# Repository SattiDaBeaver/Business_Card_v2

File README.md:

# RISC-V Supercluster Business Card

A business-card-sized PCB featuring a miniature distributed compute cluster with one master MCU coordinating eight worker nodes over a shared UART bus, powered and programmed entirely through a PCB-edge USB-C connector.

Inspired by distributed systems, Network-on-Chip architectures, and AI accelerator fabrics — shrunk down to fit in a wallet.

## Architecture

- **1× CH32X035F7P6** (master) — RV32IMAC, native USB 2.0 + USB PD PHY, USB CDC terminal, command parser, task scheduler, packet router
- **8× CH32V006F4P6** (workers) — RV32EC, distributed task execution, per-node LED, packet forwarding

## Communication

Workers and master share a half-duplex, open-drain UART bus (`BUS_MOSI` / `BUS_MISO`) with pull-up resistors to prevent contention. A simple addressed packet protocol (STX/DST/SRC/CMD/LEN/PAYLOAD/CRC8/ETX) handles routing, pings, LED control, and distributed compute tasks.

The master can individually reset and reflash any worker over UART using its factory bootloader — no physical programmer access needed after initial setup.

## Hardware Features

- USB-C via PCB edge connector (0.8mm board, no connector part needed)
- Shared 3.3V rail (AMS1117-3.3 LDO)
- Per-node SWIO/SDI debug pads for direct programming/recovery
- Individual master-controlled NRST per worker node
- Exposed GPIO test point grid on the reverse side

## Programming

- **Master:** USB bootloader or SWIO via WCH-LinkE
- **Workers:** SWIO via WCH-LinkE (initial flash) or UART bootloader via master (field updates)

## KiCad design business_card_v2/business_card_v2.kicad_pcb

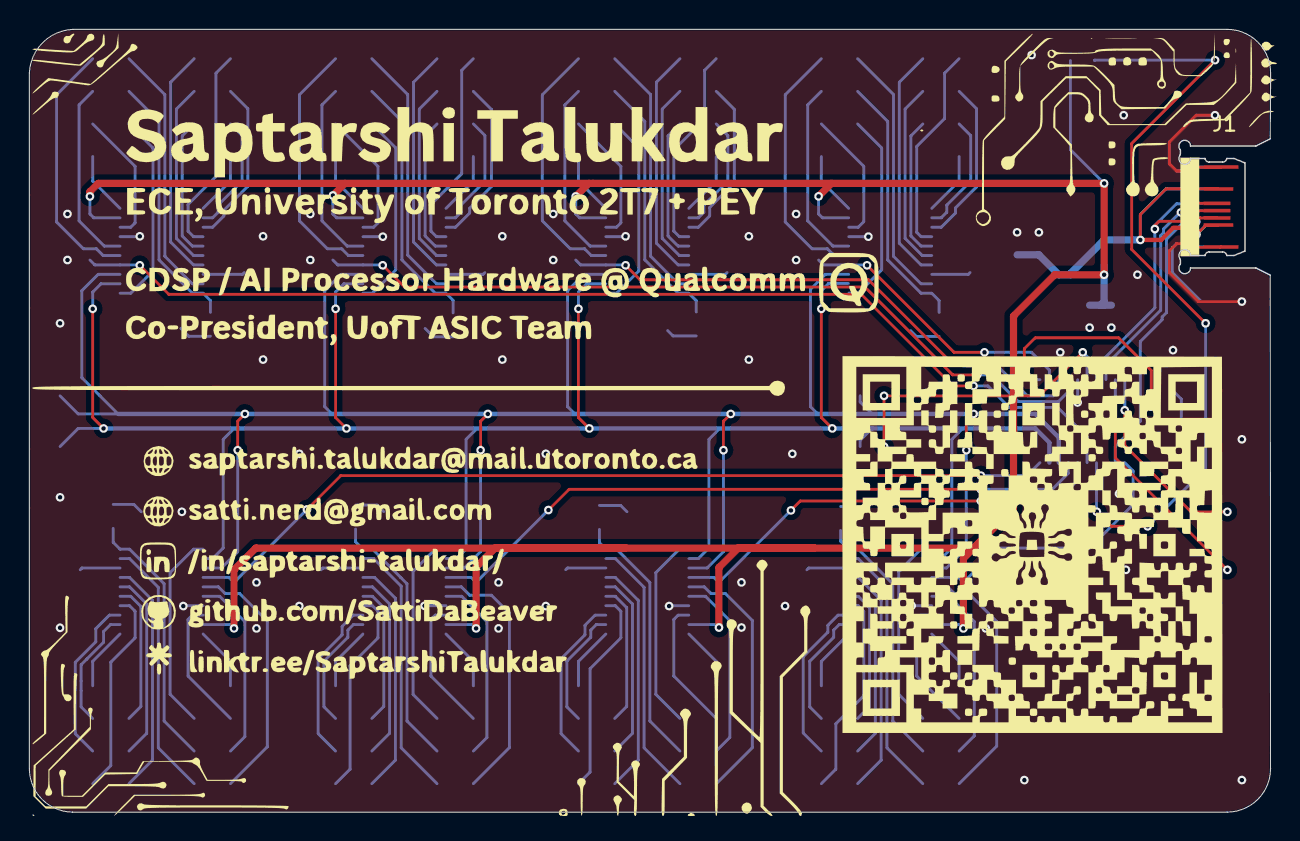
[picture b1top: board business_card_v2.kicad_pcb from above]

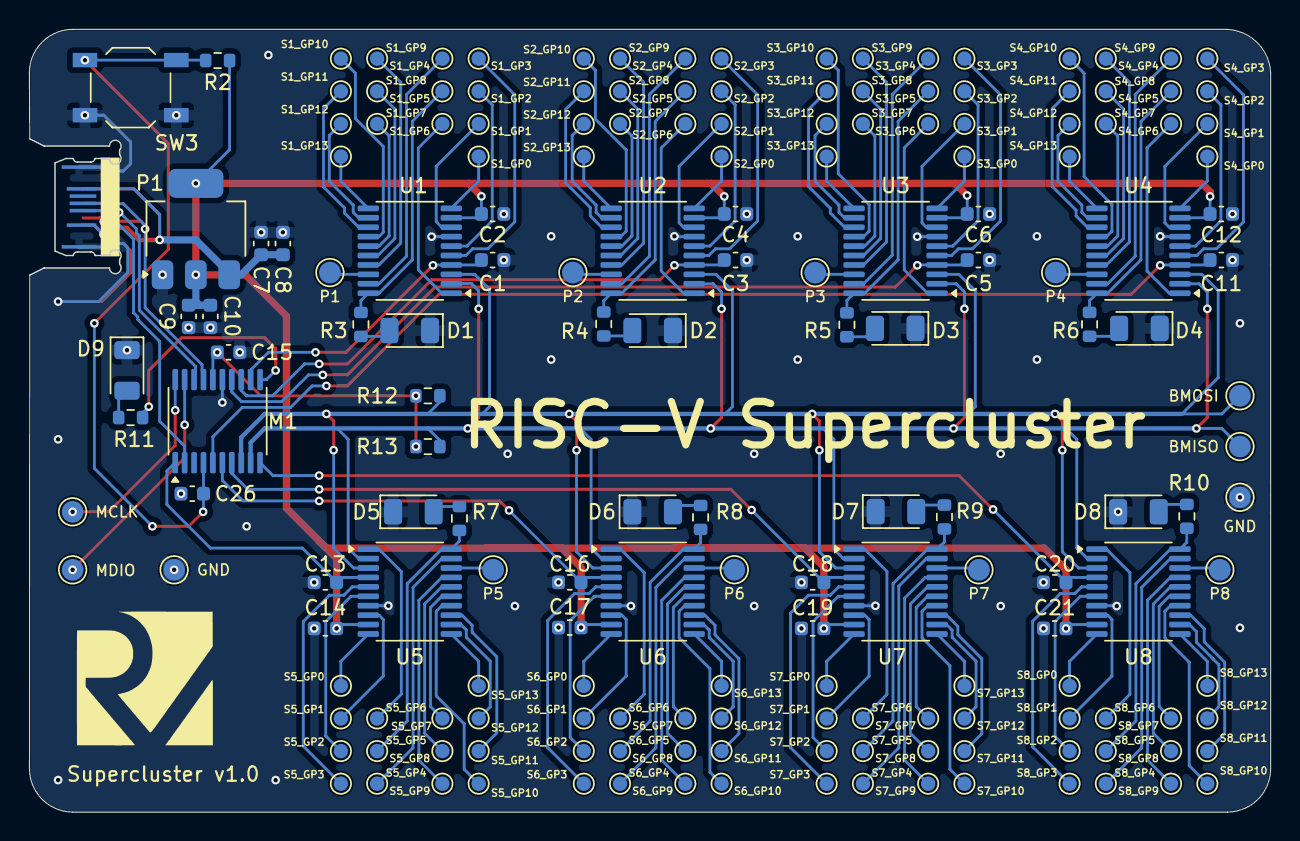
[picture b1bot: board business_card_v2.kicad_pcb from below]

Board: 2 copper layers, 85.5 x 53.9 mm, 181 parts (180 on the bottom side), 149 nets.

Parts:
BMISO: BUS_MISO; TestPoint_Pad_D1.5mm
BMOSI: BUS_MOSI; TestPoint_Pad_D1.5mm
C1, C2, C3, C4, C5, C6, C8, C9, C11, C12, C13, C14, C15, C16, C17, C18, C19, C20, C21, C26: 100nF; C_0603_1608Metric
C7, C10: 10uF; C_0603_1608Metric
D1, D2, D3, D4, D5, D6, D7, D8, D9: LED; LED_1206_3216Metric
GND: GND; TestPoint_Pad_D1.5mm
GND#2: GND; TestPoint_Pad_D1.5mm
J1: PCBTypeC_14P
M1: CH32X035F7P6; TSSOP-20_4.4x6.5mm_P0.65mm
MCLK: SWCLK_M; TestPoint_Pad_D1.5mm
MDIO: SWDIO_M; TestPoint_Pad_D1.5mm
P1: AMS1117-3.3; SOT-223-3_TabPin2
P1#2: SWIO_N1; TestPoint_Pad_D1.5mm
P2: SWIO_N2; TestPoint_Pad_D1.5mm
P3: SWIO_N3; TestPoint_Pad_D1.5mm
P4: SWIO_N4; TestPoint_Pad_D1.5mm
P5: SWIO_N5; TestPoint_Pad_D1.5mm
P6: SWIO_N6; TestPoint_Pad_D1.5mm
P7: SWIO_N7; TestPoint_Pad_D1.5mm
P8: SWIO_N8; TestPoint_Pad_D1.5mm
R2: 10k; R_0603_1608Metric
R3, R4, R5, R6, R7, R8, R9, R10, R11: 1k; R_0603_1608Metric
R12, R13: 5.1k; R_0603_1608Metric
S1_GP0, S1_GP1, S1_GP2, S1_GP3, S1_GP4, S1_GP5, S1_GP6, S1_GP7, S1_GP8, S1_GP9, S1_GP10, S1_GP11, S1_GP12, S1_GP13, S2_GP0, S2_GP1, S2_GP2, S2_GP3, S2_GP4, S2_GP5, S2_GP6, S2_GP7, S2_GP8, S2_GP9, S2_GP10, S2_GP11, S2_GP12, S2_GP13, S3_GP0, S3_GP1, S3_GP2, S3_GP3, S3_GP4, S3_GP5, S3_GP6, S3_GP7, S3_GP8, S3_GP9, S3_GP10, S3_GP11, S3_GP12, S3_GP13, S4_GP0, S4_GP1, S4_GP2, S4_GP3, S4_GP4, S4_GP5, S4_GP6, S4_GP7, S4_GP8, S4_GP9, S4_GP10, S4_GP11, S4_GP12, S4_GP13, S5_GP0, S5_GP1, S5_GP2, S5_GP3, S5_GP4, S5_GP5, S5_GP6, S5_GP7, S5_GP8, S5_GP9, S5_GP10, S5_GP11, S5_GP12, S5_GP13, S6_GP0, S6_GP1, S6_GP2, S6_GP3, S6_GP4, S6_GP5, S6_GP6, S6_GP7, S6_GP8, S6_GP9, S6_GP10, S6_GP11, S6_GP12, S6_GP13, S7_GP0, S7_GP1, S7_GP2, S7_GP3, S7_GP4, S7_GP5, S7_GP6, S7_GP7, S7_GP8, S7_GP9, S7_GP10, S7_GP11, S7_GP12, S7_GP13, S8_GP0, S8_GP1, S8_GP2, S8_GP3, S8_GP4, S8_GP5, S8_GP6, S8_GP7, S8_GP8, S8_GP9, S8_GP10, S8_GP11, S8_GP12, S8_GP13: TestPoint_Pad_D1.0mm
SW3: SW_Push; SW_SPST_TL3342
U1, U2, U3, U4, U5, U6, U7, U8: CH32V006F8P6; TSSOP-20_4.4x6.5mm_P0.65mm

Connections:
+3.3V: C2.2, C4.2, C6.2, C9.1, C10.1, C12.2, C14.2, C15.2, C17.2, C19.2, C21.2, M1.16 (VDD), P1.2 (VO), R2.2, R12.2, R13.2, U1.9 (VDD), U2.9 (VDD), U3.9 (VDD), U4.9 (VDD), U5.9 (VDD), U6.9 (VDD), U7.9 (VDD), U8.9 (VDD)
+5V: C7.1, C8.1, J1.A4 (VBUS), J1.A9 (VBUS), J1.B4 (VBUS), J1.B9 (VBUS), P1.3 (VI)
/BUS_MISO: BMISO.1 (1_1), M1.9 (PA3/RX2), R13.1, U1.2 (PD5/TX), U2.2 (PD5/TX), U3.2 (PD5/TX), U4.2 (PD5/TX), U5.2 (PD5/TX), U6.2 (PD5/TX), U7.2 (PD5/TX), U8.2 (PD5/TX)
/BUS_MOSI: BMOSI.1 (1_1), M1.8 (PA2/TX2), R12.1, U1.3 (PD6/RX), U2.3 (PD6/RX), U3.3 (PD6/RX), U4.3 (PD6/RX), U5.3 (PD6/RX), U6.3 (PD6/RX), U7.3 (PD6/RX), U8.3 (PD6/RX)
/CC1: J1.A5 (CC1), M1.2 (PC14/CC1)
/D+: J1.A6 (DP1), J1.B6 (DP2), M1.17 (PC16/UDM)
/D-: J1.A7 (DN1), J1.B7 (DN2), M1.18 (PC17/UDP)
/NRST_MASTER: C26.1, M1.4 (PC3/RST), R2.1, SW3.2
/NRST_S1: C1.1, M1.12 (PA6), U1.4 (PD7/RST)
/NRST_S2: C3.1, M1.13 (PA7), U2.4 (PD7/RST)
/NRST_S3: C5.1, M1.14 (PB1/RX4), U3.4 (PD7/RST)
/NRST_S4: C11.1, M1.5 (PC1), U4.4 (PD7/RST)
/NRST_S5: C13.1, M1.1 (PB12), U5.4 (PD7/RST)
/NRST_S6: C16.1, M1.6 (PA0), U6.4 (PD7/RST)
/NRST_S7: C18.1, M1.7 (PA1), U7.4 (PD7/RST)
/NRST_S8: C20.1, M1.10 (PA4), U8.4 (PD7/RST)
/SWCLK_M: M1.20 (PC19/DCK), MCLK.1 (1_1)
/SWDIO_M: M1.19 (PC18/DIO), MDIO.1 (1_1)
/SWIO_N1: P1#2.1 (1_1), U1.18 (PD1/SWIO)
/SWIO_N2: P2.1 (1_1), U2.18 (PD1/SWIO)
/SWIO_N3: P3.1 (1_1), U3.18 (PD1/SWIO)
/SWIO_N4: P4.1 (1_1), U4.18 (PD1/SWIO)
/SWIO_N5: P5.1 (1_1), U5.18 (PD1/SWIO)
/SWIO_N6: P6.1 (1_1), U6.18 (PD1/SWIO)
/SWIO_N7: P7.1 (1_1), U7.18 (PD1/SWIO)
/SWIO_N8: P8.1 (1_1), U8.18 (PD1/SWIO)
GND: C1.2, C2.1, C3.2, C4.1, C5.2, C6.1, C7.2, C8.2, C9.2, C10.2, C11.2, C12.1, C13.2, C14.1, C15.1, C16.2, C17.1, C18.2, C19.1, C20.2, C21.1, C26.2, D1.1 (K), D2.1 (K), D3.1 (K), D4.1 (K), D5.1 (K), D6.1 (K), D7.1 (K), D8.1 (K), D9.1 (K), GND.1 (1_1), GND#2.1 (1_1), J1.A1 (GND), J1.A12 (GND), J1.B1 (GND), J1.B12 (GND), M1.15 (GND), P1.1 (GND), SW3.1, U1.7 (VSS), U2.7 (VSS), U3.7 (VSS), U4.7 (VSS), U5.7 (VSS), U6.7 (VSS), U7.7 (VSS), U8.7 (VSS)
unnamed: D1.2 (A), R3.2
unnamed: D2.2 (A), R4.2
unnamed: D3.2 (A), R5.2
unnamed: D4.2 (A), R6.2
unnamed: D5.2 (A), R7.2
unnamed: D6.2 (A), R8.2
unnamed: D7.2 (A), R9.2
unnamed: D8.2 (A), R10.2
unnamed: D9.2 (A), R11.2
unnamed: M1.11 (PA5), R11.1
unnamed: S1_GP3.1 (1_1), U1.5 (PA1)
unnamed: S1_GP2.1 (1_1), U1.6 (PA2)
unnamed: S1_GP0.1 (1_1), U1.10 (PC0)
unnamed: S1_GP13.1 (1_1), U1.11 (PC1)
unnamed: S1_GP12.1 (1_1), U1.12 (PC2)
unnamed: S1_GP11.1 (1_1), U1.13 (PC3)
unnamed: S1_GP10.1 (1_1), U1.14 (PC4)
unnamed: S1_GP7.1 (1_1), U1.15 (PC5)
unnamed: S1_GP8.1 (1_1), U1.16 (PC6)
unnamed: S1_GP9.1 (1_1), U1.17 (PC7)
unnamed: S1_GP1.1 (1_1), U1.8 (PD0)
unnamed: S1_GP4.1 (1_1), U1.19 (PD2)
unnamed: R3.1, S1_GP5.1 (1_1), U1.20 (PD3)
unnamed: S1_GP6.1 (1_1), U1.1 (PD4)
unnamed: S2_GP3.1 (1_1), U2.5 (PA1)
unnamed: S2_GP2.1 (1_1), U2.6 (PA2)
unnamed: S2_GP0.1 (1_1), U2.10 (PC0)
unnamed: S2_GP13.1 (1_1), U2.11 (PC1)
unnamed: S2_GP12.1 (1_1), U2.12 (PC2)
unnamed: S2_GP11.1 (1_1), U2.13 (PC3)
unnamed: S2_GP10.1 (1_1), U2.14 (PC4)
unnamed: S2_GP7.1 (1_1), U2.15 (PC5)
unnamed: S2_GP8.1 (1_1), U2.16 (PC6)
unnamed: S2_GP9.1 (1_1), U2.17 (PC7)
unnamed: S2_GP1.1 (1_1), U2.8 (PD0)
unnamed: S2_GP4.1 (1_1), U2.19 (PD2)
unnamed: R4.1, S2_GP5.1 (1_1), U2.20 (PD3)
unnamed: S2_GP6.1 (1_1), U2.1 (PD4)
unnamed: S3_GP3.1 (1_1), U3.5 (PA1)
unnamed: S3_GP2.1 (1_1), U3.6 (PA2)
unnamed: S3_GP0.1 (1_1), U3.10 (PC0)
unnamed: S3_GP13.1 (1_1), U3.11 (PC1)
unnamed: S3_GP12.1 (1_1), U3.12 (PC2)
unnamed: S3_GP11.1 (1_1), U3.13 (PC3)
unnamed: S3_GP10.1 (1_1), U3.14 (PC4)
unnamed: S3_GP7.1 (1_1), U3.15 (PC5)
unnamed: S3_GP8.1 (1_1), U3.16 (PC6)
unnamed: S3_GP9.1 (1_1), U3.17 (PC7)
unnamed: S3_GP1.1 (1_1), U3.8 (PD0)
unnamed: S3_GP4.1 (1_1), U3.19 (PD2)
unnamed: R5.1, S3_GP5.1 (1_1), U3.20 (PD3)
unnamed: S3_GP6.1 (1_1), U3.1 (PD4)
unnamed: S4_GP3.1 (1_1), U4.5 (PA1)
unnamed: S4_GP2.1 (1_1), U4.6 (PA2)
unnamed: S4_GP0.1 (1_1), U4.10 (PC0)
unnamed: S4_GP13.1 (1_1), U4.11 (PC1)
unnamed: S4_GP12.1 (1_1), U4.12 (PC2)
unnamed: S4_GP11.1 (1_1), U4.13 (PC3)
unnamed: S4_GP10.1 (1_1), U4.14 (PC4)
unnamed: S4_GP7.1 (1_1), U4.15 (PC5)
unnamed: S4_GP8.1 (1_1), U4.16 (PC6)
unnamed: S4_GP9.1 (1_1), U4.17 (PC7)
unnamed: S4_GP1.1 (1_1), U4.8 (PD0)
unnamed: S4_GP4.1 (1_1), U4.19 (PD2)
unnamed: R6.1, S4_GP5.1 (1_1), U4.20 (PD3)
unnamed: S4_GP6.1 (1_1), U4.1 (PD4)
unnamed: S5_GP3.1 (1_1), U5.5 (PA1)
unnamed: S5_GP2.1 (1_1), U5.6 (PA2)
unnamed: S5_GP0.1 (1_1), U5.10 (PC0)
unnamed: S5_GP13.1 (1_1), U5.11 (PC1)
unnamed: S5_GP12.1 (1_1), U5.12 (PC2)
unnamed: S5_GP11.1 (1_1), U5.13 (PC3)
unnamed: S5_GP10.1 (1_1), U5.14 (PC4)
unnamed: S5_GP7.1 (1_1), U5.15 (PC5)
unnamed: S5_GP8.1 (1_1), U5.16 (PC6)
unnamed: S5_GP9.1 (1_1), U5.17 (PC7)
unnamed: S5_GP1.1 (1_1), U5.8 (PD0)
unnamed: S5_GP4.1 (1_1), U5.19 (PD2)
unnamed: R7.1, S5_GP5.1 (1_1), U5.20 (PD3)
unnamed: S5_GP6.1 (1_1), U5.1 (PD4)
unnamed: S6_GP3.1 (1_1), U6.5 (PA1)
unnamed: S6_GP2.1 (1_1), U6.6 (PA2)
unnamed: S6_GP0.1 (1_1), U6.10 (PC0)
unnamed: S6_GP13.1 (1_1), U6.11 (PC1)
unnamed: S6_GP12.1 (1_1), U6.12 (PC2)
unnamed: S6_GP11.1 (1_1), U6.13 (PC3)
unnamed: S6_GP10.1 (1_1), U6.14 (PC4)
unnamed: S6_GP7.1 (1_1), U6.15 (PC5)
unnamed: S6_GP8.1 (1_1), U6.16 (PC6)
unnamed: S6_GP9.1 (1_1), U6.17 (PC7)
unnamed: S6_GP1.1 (1_1), U6.8 (PD0)
unnamed: S6_GP4.1 (1_1), U6.19 (PD2)
unnamed: R8.1, S6_GP5.1 (1_1), U6.20 (PD3)
unnamed: S6_GP6.1 (1_1), U6.1 (PD4)
unnamed: S7_GP3.1 (1_1), U7.5 (PA1)
unnamed: S7_GP2.1 (1_1), U7.6 (PA2)
unnamed: S7_GP0.1 (1_1), U7.10 (PC0)
unnamed: S7_GP13.1 (1_1), U7.11 (PC1)
unnamed: S7_GP12.1 (1_1), U7.12 (PC2)
unnamed: S7_GP11.1 (1_1), U7.13 (PC3)
unnamed: S7_GP10.1 (1_1), U7.14 (PC4)
unnamed: S7_GP7.1 (1_1), U7.15 (PC5)
unnamed: S7_GP8.1 (1_1), U7.16 (PC6)
unnamed: S7_GP9.1 (1_1), U7.17 (PC7)
unnamed: S7_GP1.1 (1_1), U7.8 (PD0)
unnamed: S7_GP4.1 (1_1), U7.19 (PD2)
unnamed: R9.1, S7_GP5.1 (1_1), U7.20 (PD3)
unnamed: S7_GP6.1 (1_1), U7.1 (PD4)
unnamed: S8_GP3.1 (1_1), U8.5 (PA1)
unnamed: S8_GP2.1 (1_1), U8.6 (PA2)
unnamed: S8_GP0.1 (1_1), U8.10 (PC0)
unnamed: S8_GP13.1 (1_1), U8.11 (PC1)
unnamed: S8_GP12.1 (1_1), U8.12 (PC2)
unnamed: S8_GP11.1 (1_1), U8.13 (PC3)
unnamed: S8_GP10.1 (1_1), U8.14 (PC4)
unnamed: S8_GP7.1 (1_1), U8.15 (PC5)
unnamed: S8_GP8.1 (1_1), U8.16 (PC6)
unnamed: S8_GP9.1 (1_1), U8.17 (PC7)
unnamed: S8_GP1.1 (1_1), U8.8 (PD0)
unnamed: S8_GP4.1 (1_1), U8.19 (PD2)
unnamed: R10.1, S8_GP5.1 (1_1), U8.20 (PD3)
unnamed: S8_GP6.1 (1_1), U8.1 (PD4)

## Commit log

2026-05-29 created ch32 symbols. added PCB USBC, created board outline
2026-05-29 history?
2026-06-12 bottom left to top right pins
2026-06-12 9 S1 pins pattern
2026-06-14 added basic traces
2026-06-14 first commit: removed 1 MCU
2026-06-15 wired all GPIO
2026-06-16 added reset wires and bus
2026-06-19 finalized PCB
2026-06-19 Remove .history from tracking
2026-06-19 added README
